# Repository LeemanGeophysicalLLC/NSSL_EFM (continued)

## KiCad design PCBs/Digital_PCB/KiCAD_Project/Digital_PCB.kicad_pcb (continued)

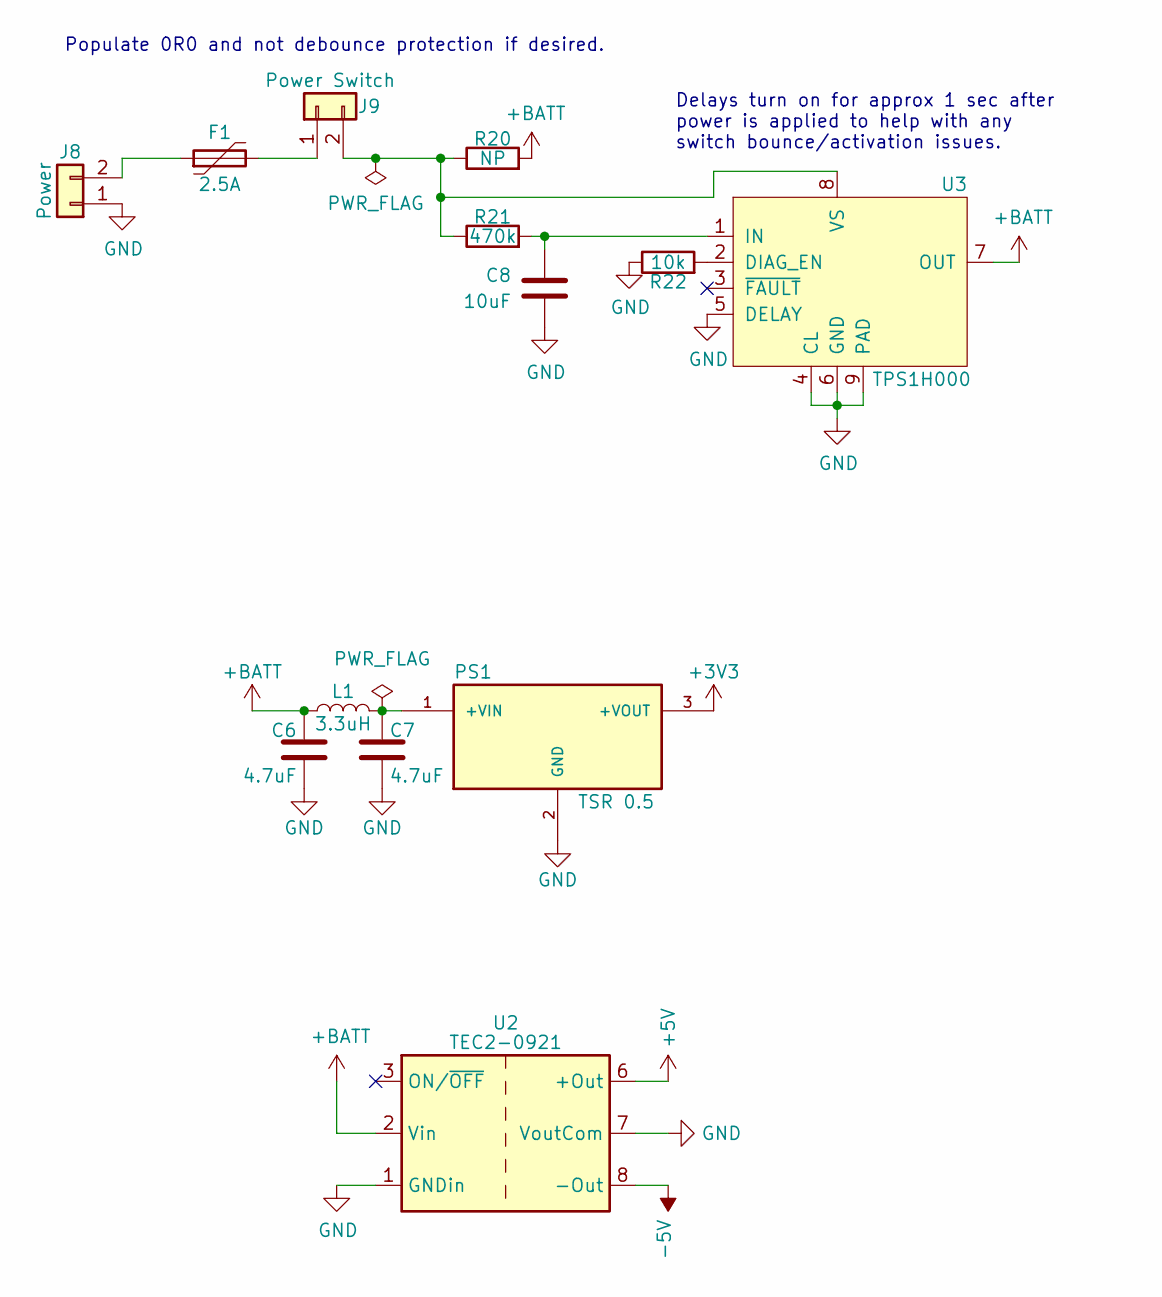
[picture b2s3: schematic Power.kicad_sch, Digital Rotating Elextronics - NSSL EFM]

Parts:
C6, C7: 1-0000136
C8: 1-0000075
F1: 1-0000269
J8, J9: NP_Conn_01x02_Relief; SolderWire_1x02_Relief
L1: 1-0000931
PS1: 1-0000727
R20: 1-0000006
R21: 1-0000068
R22: 1-0000010
U2: 1-0000465
U3: 1-0000576

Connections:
+3V3: PS1.3 (+VOUT); also elsewhere on the board
+5V: U2.6 (+Out); also elsewhere on the board
+BATT: C6.1, L1.1, R20.2, U2.2 (Vin), U3.7 (OUT); also elsewhere on the board
-5V: U2.8 (-Out); also elsewhere on the board
GND: C6.2, C7.2, C8.1, J8.1, PS1.2 (GND), R22.1, U2.1 (GNDin), U2.7 (VoutCom), U3.4 (CL), U3.5 (DELAY), U3.6 (GND), U3.9 (PAD); also elsewhere on the board
unnamed: F1.1, J8.2
unnamed: F1.2, J9.1
unnamed: J9.2, R20.1, R21.1, U3.8 (VS)
unnamed: C7.1, L1.2, PS1.1 (+VIN)
unnamed: R22.2, U3.2 (DIAG_EN)
unnamed: C8.2, R21.2, U3.1 (IN)

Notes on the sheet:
Populate 0R0 and not debounce protection if desired.
Delays turn on for approx 1 sec after power is applied to help with any switch bounce/activation issues.

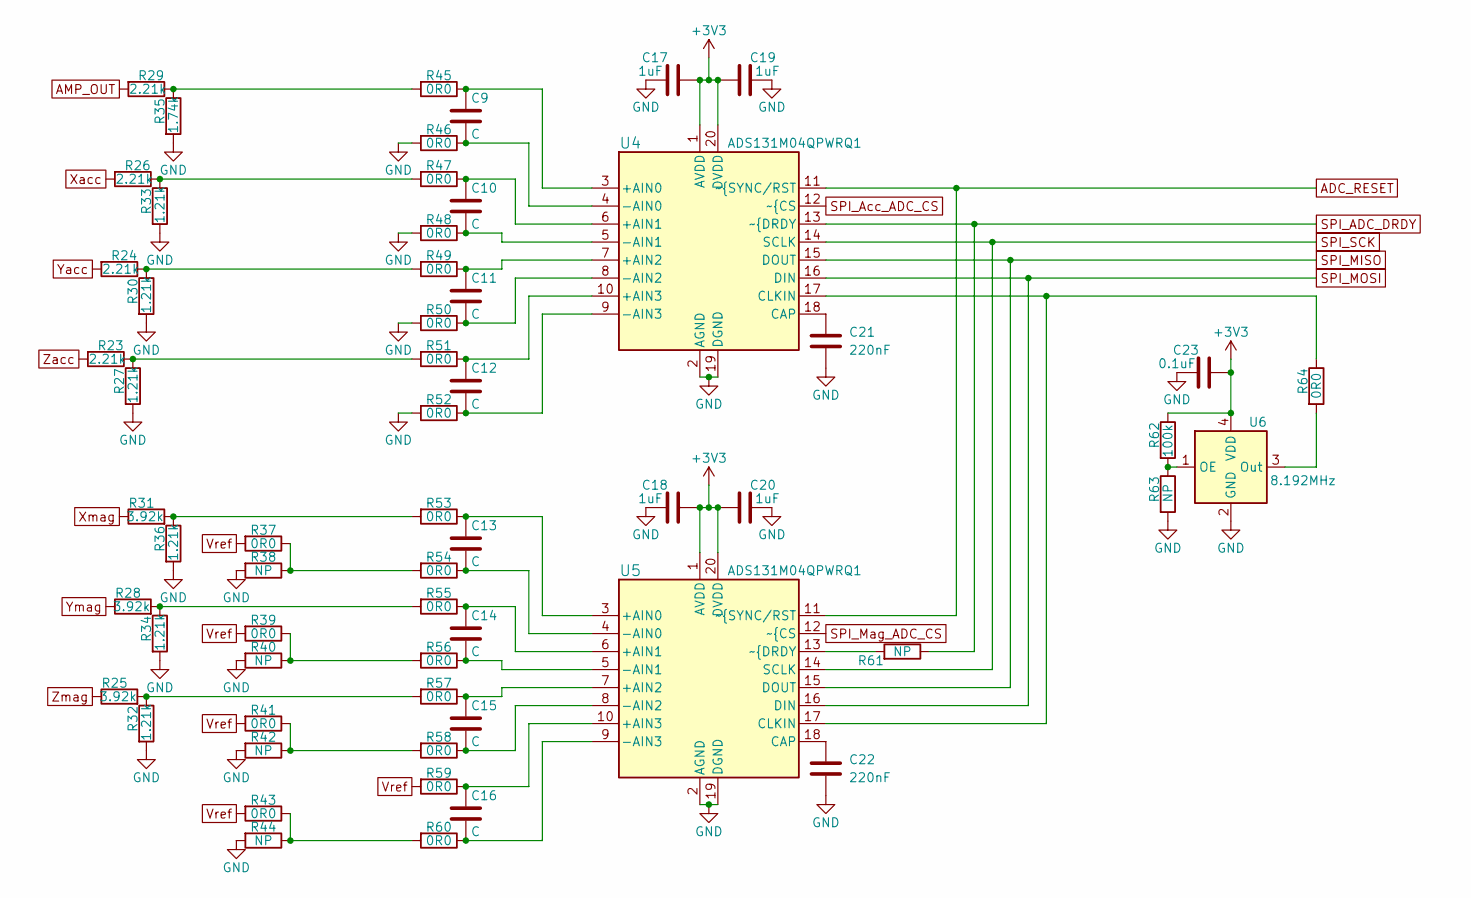
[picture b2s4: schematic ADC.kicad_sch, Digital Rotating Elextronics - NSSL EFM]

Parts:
C9, C10, C11, C12, C13, C14, C15, C16: C; C_0603_1608Metric
C17, C18, C19, C20: 1-0000018
C21, C22: 1-0000926
C23: 1-0000007
R23, R24, R26, R29: 1-0001551
R25, R28, R31: 1-0001554
R27, R30, R32, R33, R34, R36: 1-0001553
R35: 1-0001552
R37, R38, R39, R40, R41, R42, R43, R44, R45, R46, R47, R48, R49, R50, R51, R52, R53, R54, R55, R56, R57, R58, R59, R60, R61, R63, R64: 1-0000006
R62: 1-0000174
U4, U5: 1-0001530
U6: 1-0001542

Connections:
+3V3: C17.1, C18.1, C19.1, C20.1, C23.2, R62.1, U4.1 (AVDD), U4.20 (DVDD), U5.1 (AVDD), U5.20 (DVDD), U6.4 (VDD); also elsewhere on the board
ADC_RESET: U4.11 (~{SYNC/RST), U5.11 (~{SYNC/RST); also elsewhere on the board
AMP_OUT: R29.2; also elsewhere on the board
GND: C17.2, C18.2, C19.2, C20.2, C21.2, C22.2, C23.1, R27.2, R30.2, R32.2, R33.2, R34.2, R35.2, R36.2, R38.2, R40.2, R42.2, R44.2, R46.2, R48.2, R50.2, R52.2, R63.2, U4.2 (AGND), U4.19 (DGND), U5.2 (AGND), U5.19 (DGND), U6.2 (GND); also elsewhere on the board
unnamed: R23.1, R27.1, R51.2
unnamed: R24.1, R30.1, R49.2
unnamed: R25.2, R32.1, R57.2
unnamed: R26.1, R33.1, R47.2
unnamed: R28.2, R34.1, R55.2
unnamed: R29.1, R35.1, R45.2
unnamed: R31.2, R36.1, R53.2
unnamed: R37.1, R38.1, R54.2
unnamed: R39.1, R40.1, R56.2
unnamed: R41.1, R42.1, R58.2
unnamed: R43.1, R44.1, R60.2
unnamed: C9.1, R45.1, U4.3 (+AIN0)
unnamed: C10.1, R47.1, U4.6 (+AIN1)
unnamed: C11.1, R49.1, U4.7 (+AIN2)
unnamed: C12.1, R51.1, U4.10 (+AIN3)
unnamed: C9.2, R46.1, U4.4 (-AIN0)
unnamed: C10.2, R48.1, U4.5 (-AIN1)
unnamed: C11.2, R50.1, U4.8 (-AIN2)
unnamed: C12.2, R52.1, U4.9 (-AIN3)
unnamed: C21.1, U4.18 (CAP)
unnamed: R64.1, U4.17 (CLKIN), U5.17 (CLKIN)
unnamed: C13.1, R53.1, U5.3 (+AIN0)
unnamed: C14.1, R55.1, U5.6 (+AIN1)
unnamed: C15.1, R57.1, U5.7 (+AIN2)
unnamed: C16.1, R59.1, U5.10 (+AIN3)
unnamed: C13.2, R54.1, U5.4 (-AIN0)
unnamed: C14.2, R56.1, U5.5 (-AIN1)
unnamed: C15.2, R58.1, U5.8 (-AIN2)
unnamed: C16.2, R60.1, U5.9 (-AIN3)
unnamed: C22.1, U5.18 (CAP)
unnamed: R61.2, U5.13 (~{DRDY)
unnamed: R62.2, R63.1, U6.1 (OE)
unnamed: R64.2, U6.3 (Out)
SPI_ADC_DRDY: R61.1, U4.13 (~{DRDY); also elsewhere on the board
SPI_Acc_ADC_CS: U4.12 (~{CS); also elsewhere on the board
SPI_MISO: U4.15 (DOUT), U5.15 (DOUT); also elsewhere on the board
SPI_MOSI: U4.16 (DIN), U5.16 (DIN); also elsewhere on the board
SPI_Mag_ADC_CS: U5.12 (~{CS); also elsewhere on the board
SPI_SCK: U4.14 (SCLK), U5.14 (SCLK); also elsewhere on the board
Vref: R37.2, R39.2, R41.2, R43.2, R59.2; also elsewhere on the board
Xacc: R26.2; also elsewhere on the board
Xmag: R31.1; also elsewhere on the board
Yacc: R24.2; also elsewhere on the board
Ymag: R28.1; also elsewhere on the board
Zacc: R23.2; also elsewhere on the board
Zmag: R25.1; also elsewhere on the board

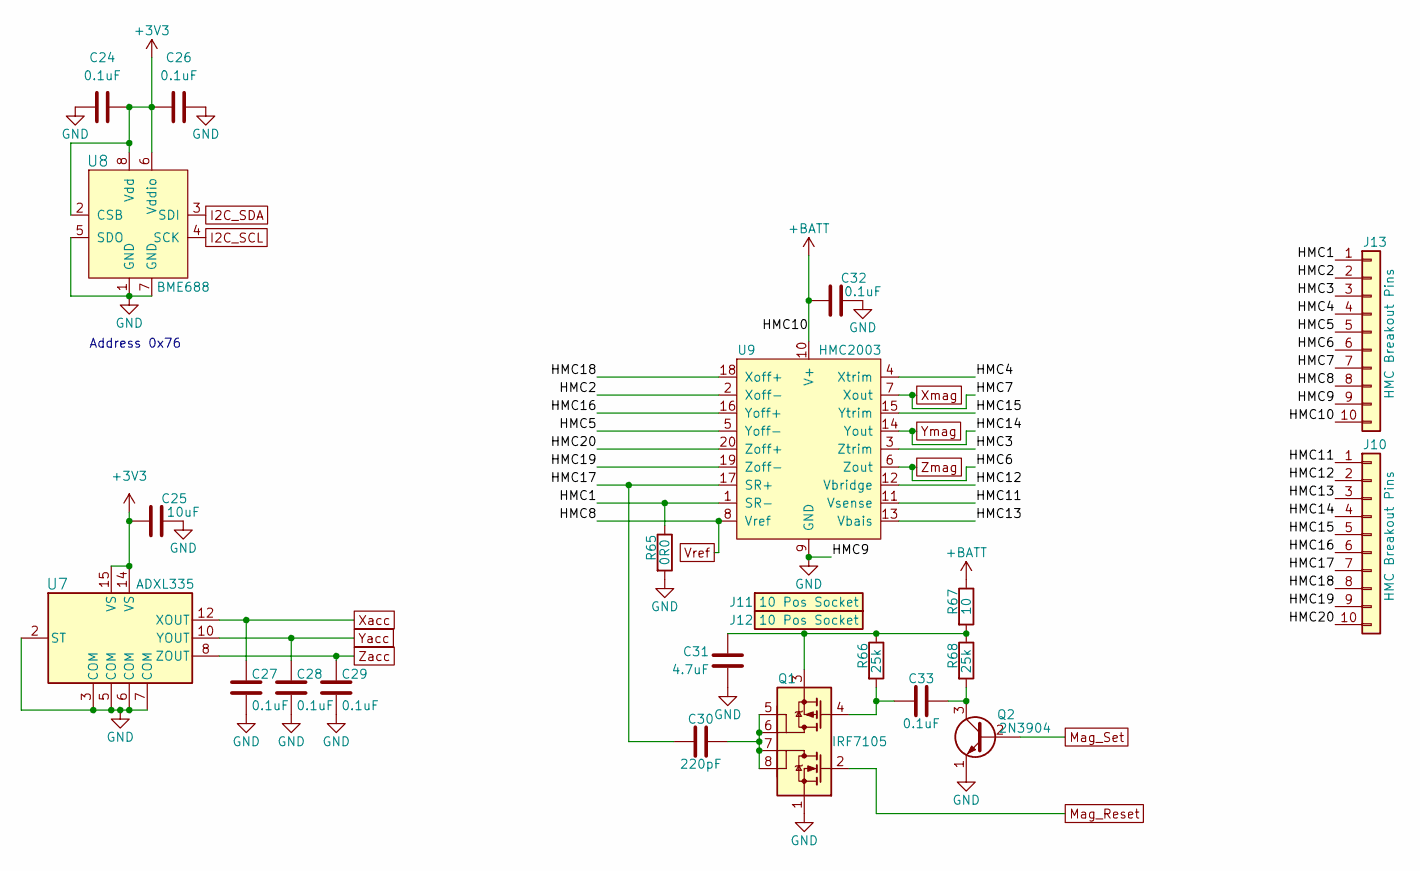
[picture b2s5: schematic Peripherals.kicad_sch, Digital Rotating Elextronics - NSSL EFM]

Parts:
C24, C26, C27, C28, C29, C32, C33: 1-0000007
C25: 1-0000075
C30: 1-0000322
C31: 1-0000136
J10, J13: HMC Breakout Pins; PinHeader_1x10_P2.54mm_Vertical
J11, J12: 1-0001555
Q1: 1-0001548
Q2: 1-0001214
R65: 1-0000006
R66, R68: 1-0001549
R67: 1-0001528
U7: 1-0001535
U8: 1-0001471
U9: 1-0001543

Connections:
+3V3: C24.2, C25.1, C26.1, U7.14 (VS), U7.15 (VS), U8.2 (CSB), U8.6 (Vddio), U8.8 (Vdd); also elsewhere on the board
+BATT: C32.1, J13.10, R67.1, U9.10 (V+); also elsewhere on the board
/Peripherals/HMC1: J13.1, R65.1, U9.1 (SR-)
/Peripherals/HMC2: J13.2, U9.2 (Xoff-)
/Peripherals/HMC3: J13.3, U9.3 (Ztrim)
/Peripherals/HMC4: J13.4, U9.4 (Xtrim)
/Peripherals/HMC5: J13.5, U9.5 (Yoff-)
/Peripherals/HMC11: J10.1, U9.11 (Vsense)
/Peripherals/HMC12: J10.2, U9.12 (Vbridge)
/Peripherals/HMC13: J10.3, U9.13 (Vbais)
/Peripherals/HMC15: J10.5, U9.15 (Ytrim)
/Peripherals/HMC16: J10.6, U9.16 (Yoff+)
/Peripherals/HMC17: C30.1, J10.7, U9.17 (SR+)
/Peripherals/HMC18: J10.8, U9.18 (Xoff+)
/Peripherals/HMC19: J10.9, U9.19 (Zoff-)
/Peripherals/HMC20: J10.10, U9.20 (Zoff+)
GND: C24.1, C25.2, C26.2, C27.2, C28.2, C29.2, C31.2, C32.2, J13.9, Q1.1 (S1), Q2.1 (E), R65.2, U7.2 (ST), U7.3 (COM), U7.5 (COM), U7.6 (COM), U7.7 (COM), U8.1 (GND), U8.5 (SDO), U8.7 (GND), U9.9 (GND); also elsewhere on the board
I2C_SCL: U8.4 (SCK); also elsewhere on the board
I2C_SDA: U8.3 (SDI); also elsewhere on the board
Mag_Reset: Q1.2 (G1); also elsewhere on the board
Mag_Set: Q2.2 (B); also elsewhere on the board
unnamed: C30.2, Q1.5 (D2), Q1.6 (D2), Q1.7 (D1), Q1.8 (D1)
unnamed: C33.1, Q1.4 (G2), R66.2
unnamed: C31.1, Q1.3 (S2), R66.1, R67.2, R68.1
unnamed: C33.2, Q2.3 (C), R68.2
Vref: J13.8, U9.8 (Vref); also elsewhere on the board
Xacc: C27.1, U7.12 (XOUT); also elsewhere on the board
Xmag: J13.7, U9.7 (Xout); also elsewhere on the board
Yacc: C28.1, U7.10 (YOUT); also elsewhere on the board
Ymag: J10.4, U9.14 (Yout); also elsewhere on the board
Zacc: C29.1, U7.8 (ZOUT); also elsewhere on the board
Zmag: J13.6, U9.6 (Zout); also elsewhere on the board

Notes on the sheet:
Address 0x76

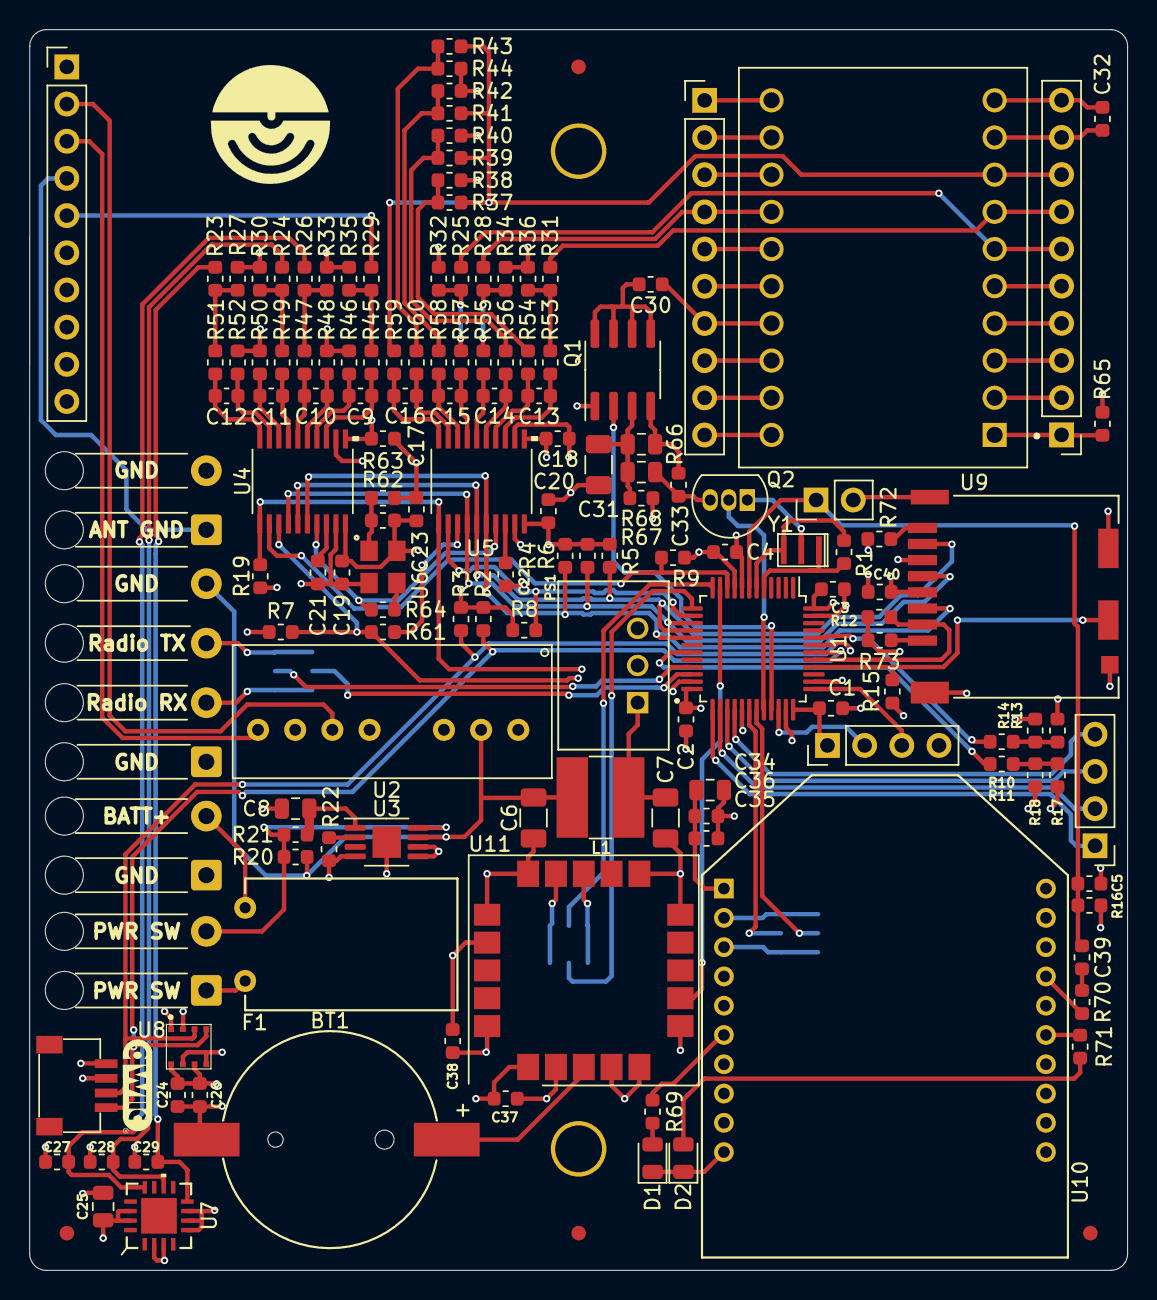
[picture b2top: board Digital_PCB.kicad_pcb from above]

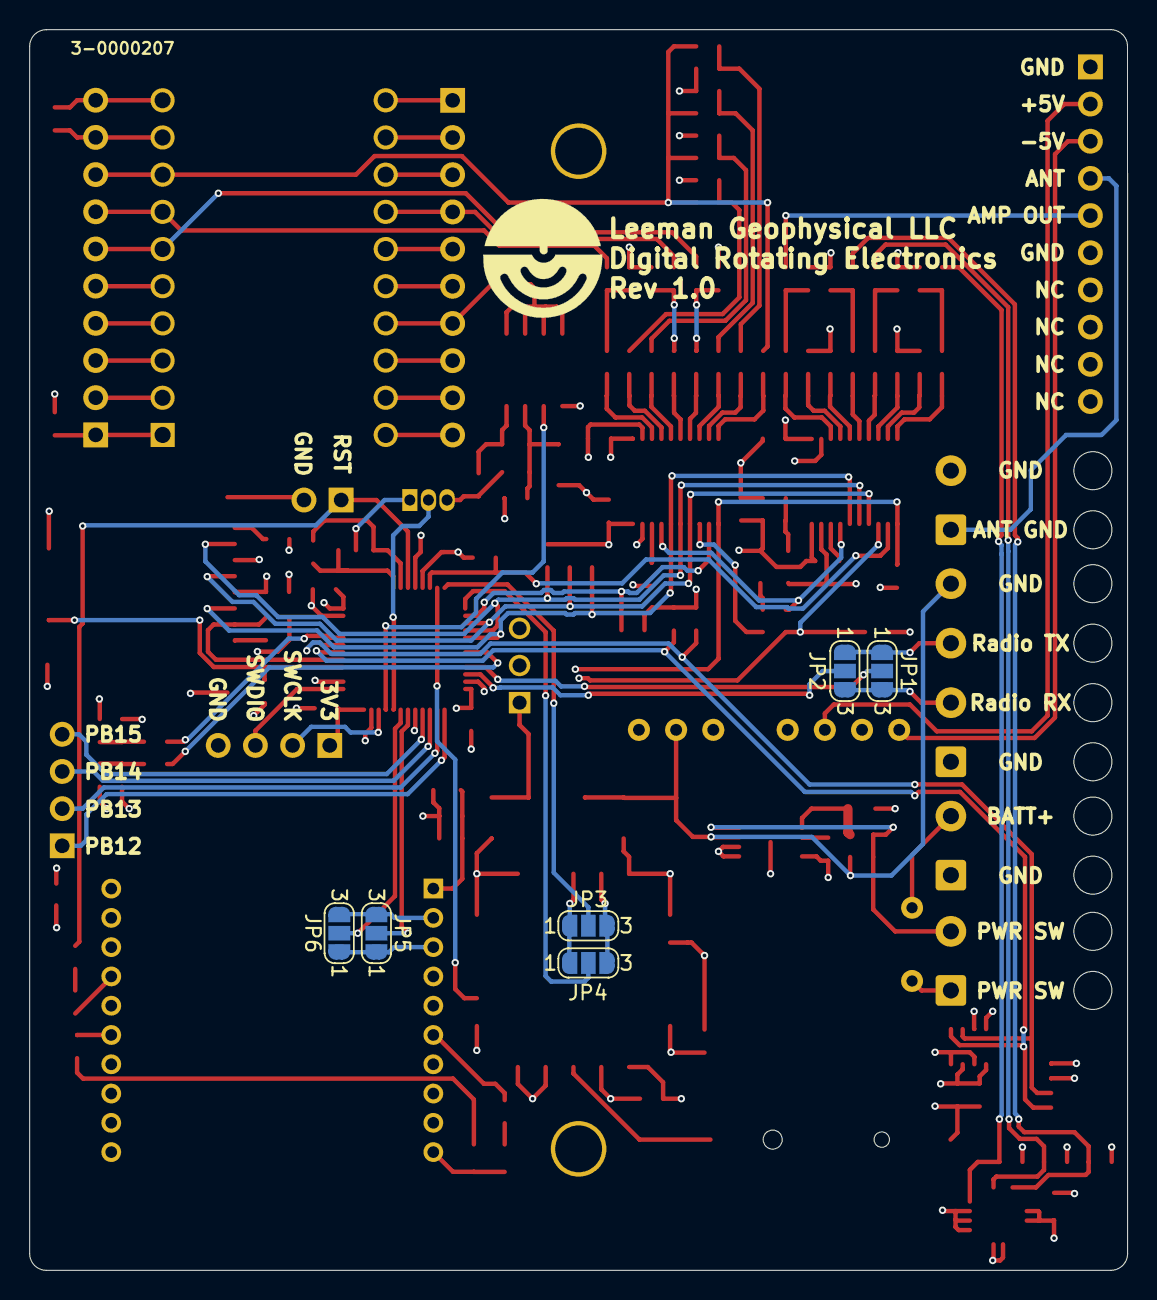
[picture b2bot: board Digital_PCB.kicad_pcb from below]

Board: 4 copper layers, 75.0 x 84.8 mm, 161 parts (6 on the bottom side), 119 nets.

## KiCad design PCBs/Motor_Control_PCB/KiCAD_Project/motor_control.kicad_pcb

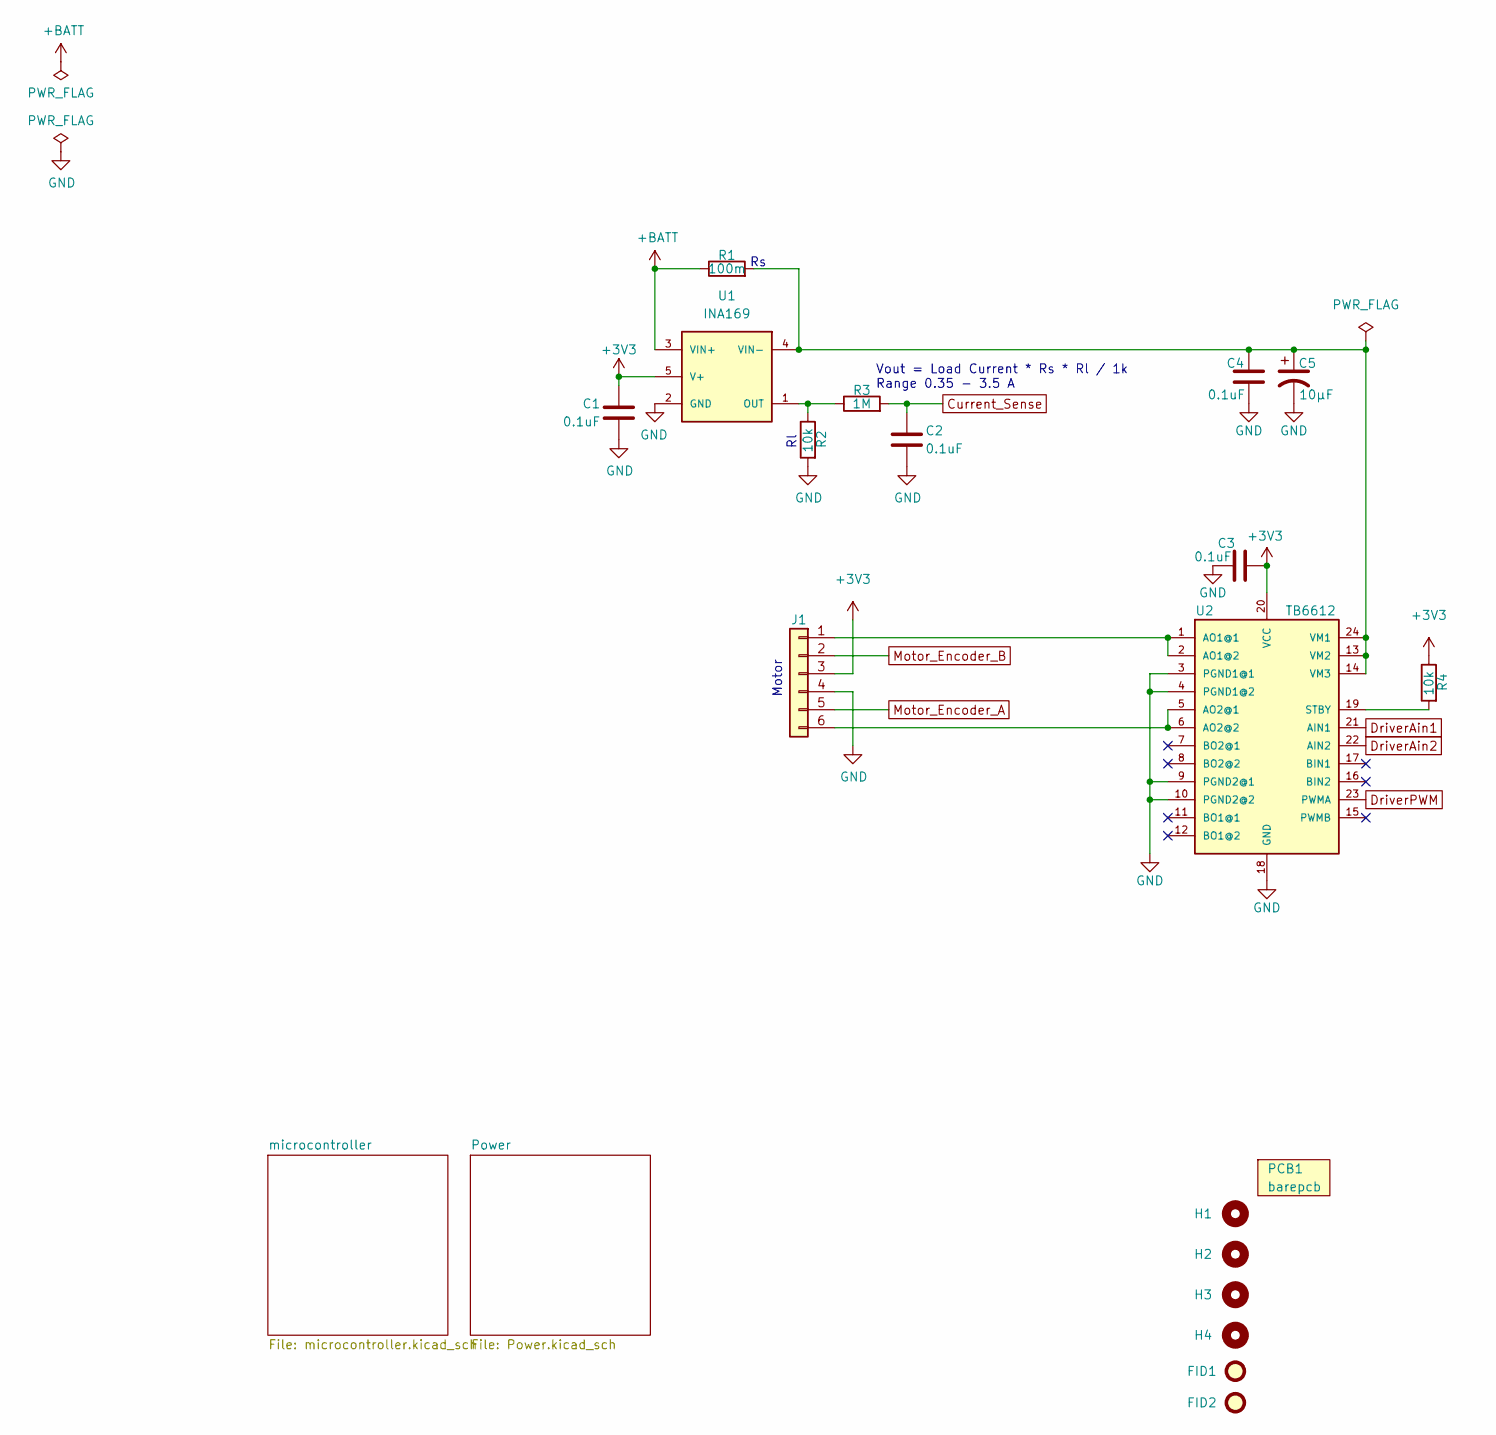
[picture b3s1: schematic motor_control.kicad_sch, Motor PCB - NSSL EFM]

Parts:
C1, C2, C3, C4: 1-0000007
C5: 1-0000176
FID1, FID2: Fiducial_1mm_2mm; Fiducial_1mm_Mask2mm
H1, H2, H3, H4: Imperial4; MountingHole_imperial4
J1: NP_Conn_01x06; PinHeader_1x06_P2.54mm_Vertical
PCB1: barepcb
R1: 1-0001546
R2, R4: 1-0000010
R3: 1-0000009
U1: 1-0000452
U2: 1-0001532

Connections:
+3V3: C1.1, C3.2, J1.3, R4.1, U1.5 (V+), U2.20 (VCC); also elsewhere on the board
+BATT: R1.1, U1.3 (VIN+); also elsewhere on the board
Current_Sense: C2.1, R3.2; also elsewhere on the board
DriverAin1: U2.21 (AIN1); also elsewhere on the board
DriverAin2: U2.22 (AIN2); also elsewhere on the board
DriverPWM: U2.23 (PWMA); also elsewhere on the board
GND: C1.2, C2.2, C3.1, C4.1, C5.2, J1.4, R2.2, U1.2 (GND), U2.3 (PGND1@1), U2.4 (PGND1@2), U2.9 (PGND2@1), U2.10 (PGND2@2), U2.18 (GND); also elsewhere on the board
Motor_Encoder_A: J1.5; also elsewhere on the board
Motor_Encoder_B: J1.2; also elsewhere on the board
unnamed: J1.1, U2.1 (AO1@1), U2.2 (AO1@2)
unnamed: J1.6, U2.5 (AO2@1), U2.6 (AO2@2)
unnamed: R2.1, R3.1, U1.1 (OUT)
unnamed: C4.2, C5.1, R1.2, U1.4 (VIN-), U2.13 (VM2), U2.14 (VM3), U2.24 (VM1)
unnamed: R4.2, U2.19 (STBY)

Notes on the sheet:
Motor
Vout = Load Current * Rs * Rl / 1k Range 0.35 - 3.5 A

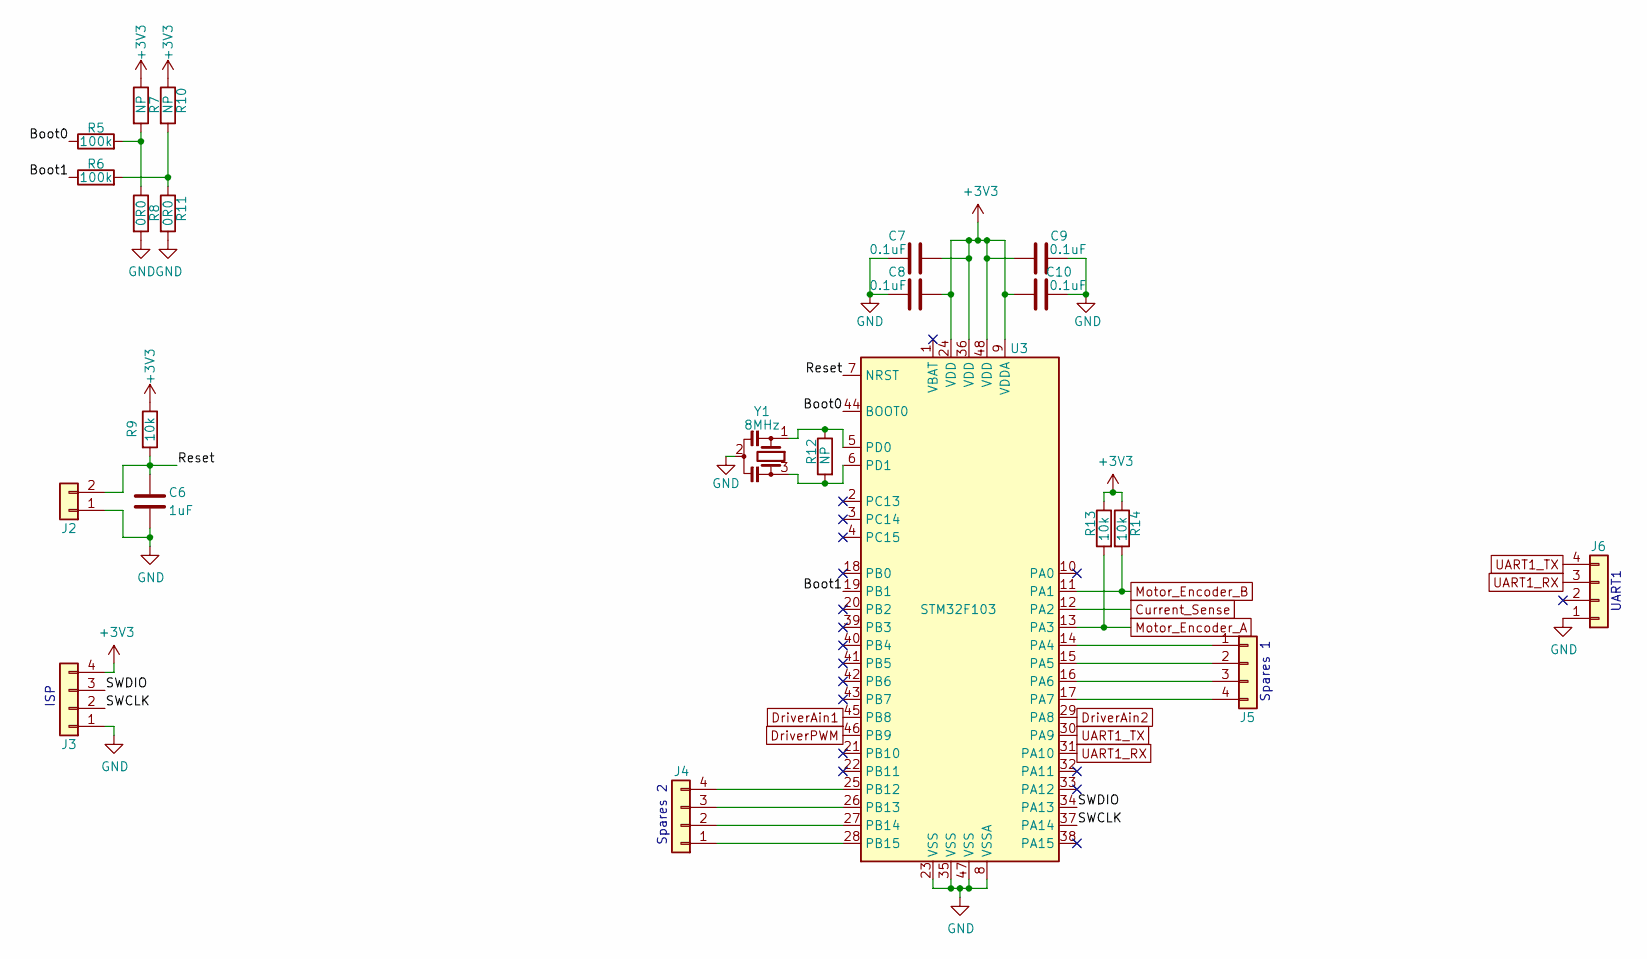
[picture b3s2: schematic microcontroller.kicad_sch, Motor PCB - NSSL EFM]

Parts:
C6: 1-0000018
C7, C8, C9, C10: 1-0000007
J2: NP_Conn_01x02; PinHeader_1x02_P2.54mm_Vertical
J3, J4, J5, J6: NP_Conn_01x04; PinHeader_1x04_P2.54mm_Vertical
R5, R6: 1-0000174
R7, R8, R10, R11, R12: 1-0000006
R9, R13, R14: 1-0000010
U3: 1-0000207
Y1: 1-0000721

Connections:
+3V3: C7.1, C8.1, C9.1, C10.1, J3.4, R7.1, R9.1, R10.1, R13.1, R14.1, U3.9 (VDDA), U3.24 (VDD), U3.36 (VDD), U3.48 (VDD); also elsewhere on the board
/microcontroller/Boot0: R5.1, U3.44 (BOOT0)
/microcontroller/Boot1: R6.1, U3.19 (PB1)
/microcontroller/Reset: C6.1, J2.2, R9.2, U3.7 (NRST)
/microcontroller/SWCLK: J3.2, U3.37 (PA14)
/microcontroller/SWDIO: J3.3, U3.34 (PA13)
Current_Sense: U3.12 (PA2); also elsewhere on the board
DriverAin1: U3.45 (PB8); also elsewhere on the board
DriverAin2: U3.29 (PA8); also elsewhere on the board
DriverPWM: U3.46 (PB9); also elsewhere on the board
GND: C6.2, C7.2, C8.2, C9.2, C10.2, J2.1, J3.1, J6.1, R8.2, R11.2, U3.8 (VSSA), U3.23 (VSS), U3.35 (VSS), U3.47 (VSS), Y1.2; also elsewhere on the board
Motor_Encoder_A: R13.2, U3.13 (PA3); also elsewhere on the board
Motor_Encoder_B: R14.2, U3.11 (PA1); also elsewhere on the board
unnamed: J4.1, U3.28 (PB15)
unnamed: J4.2, U3.27 (PB14)
unnamed: J4.3, U3.26 (PB13)
unnamed: J4.4, U3.25 (PB12)
unnamed: J5.1, U3.14 (PA4)
unnamed: J5.2, U3.15 (PA5)
unnamed: J5.3, U3.16 (PA6)
unnamed: J5.4, U3.17 (PA7)
unnamed: R5.2, R7.2, R8.1
unnamed: R6.2, R10.2, R11.1
unnamed: R12.1, U3.5 (PD0), Y1.1
unnamed: R12.2, U3.6 (PD1), Y1.3
UART1_RX: J6.3, U3.31 (PA10)
UART1_TX: J6.4, U3.30 (PA9)

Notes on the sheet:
Spares 1
UART1
Spares 2
ISP

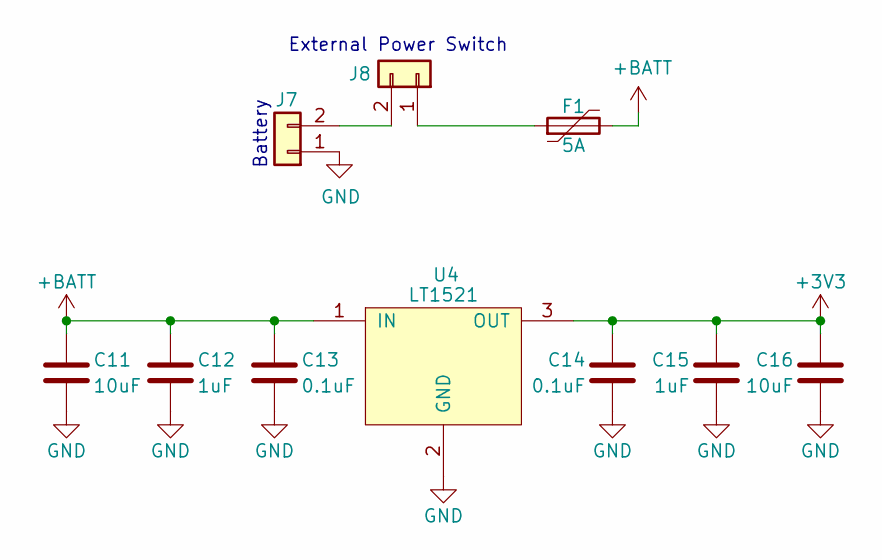
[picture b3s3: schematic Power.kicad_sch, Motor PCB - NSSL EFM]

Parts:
C11, C16: 1-0000005
C12, C15: 1-0000018
C13, C14: 1-0000007
F1: 1-0001547
J7, J8: NP_Conn_01x02_Relief; SolderWire_1x02_Relief
U4: 1-0000196

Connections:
+3V3: C14.1, C15.1, C16.1, U4.3 (OUT); also elsewhere on the board
+BATT: C11.1, C12.1, C13.1, F1.2, U4.1 (IN); also elsewhere on the board
GND: C11.2, C12.2, C13.2, C14.2, C15.2, C16.2, J7.1, U4.2 (GND); also elsewhere on the board
unnamed: J7.2, J8.2
unnamed: F1.1, J8.1

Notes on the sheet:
Battery
External Power Switch

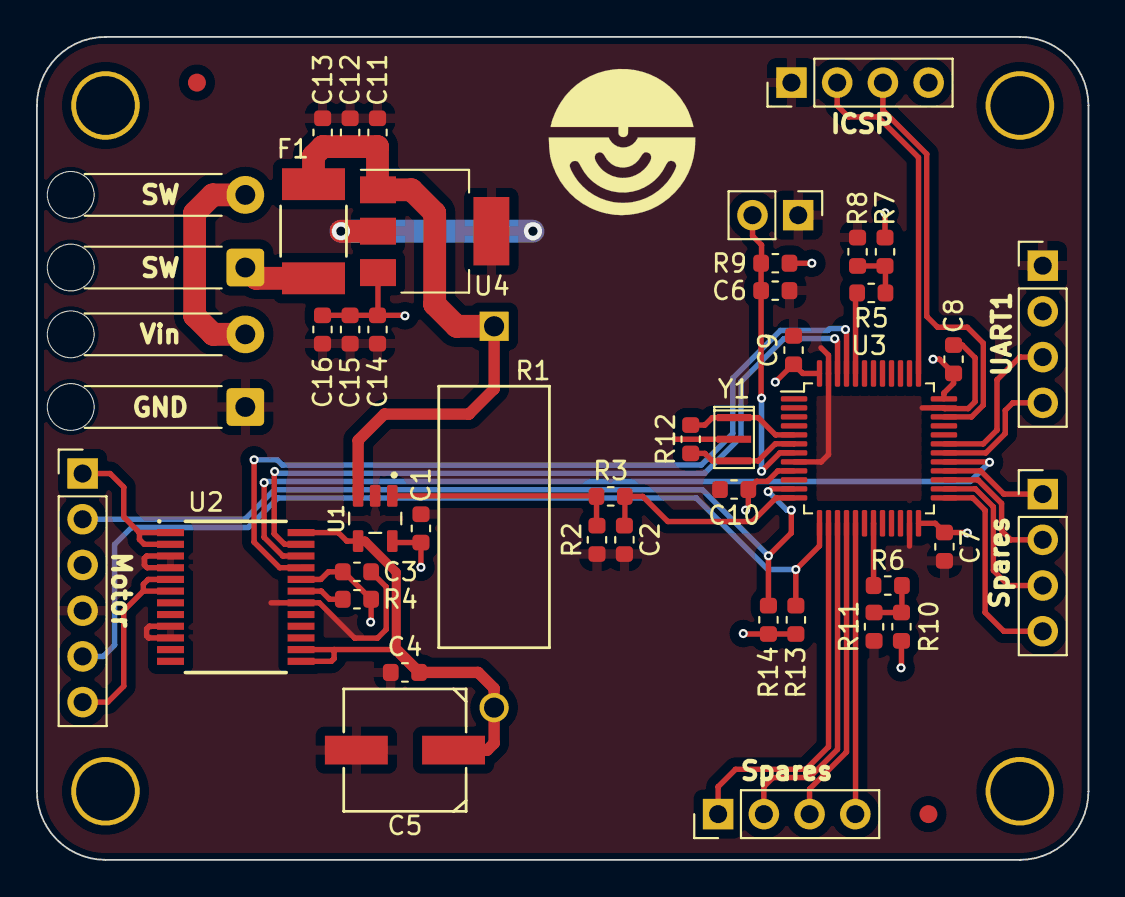
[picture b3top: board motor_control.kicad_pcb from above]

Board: 4 copper layers, 58.4 x 45.7 mm, 51 parts (0 on the bottom side), 35 nets.

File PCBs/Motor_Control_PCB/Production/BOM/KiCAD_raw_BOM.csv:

"Reference","Value","Datasheet","Footprint","Qty","Internal Part Number","PValue","Populated"
"C1","1-0000007","~","capacitors_0603:1-0000007","1","1-0000007","0.1uF","1"
"C2","1-0000007","~","capacitors_0603:1-0000007","1","1-0000007","0.1uF","1"
"C3","1-0000007","~","capacitors_0603:1-0000007","1","1-0000007","0.1uF","1"
"C4","1-0000007","~","capacitors_0603:1-0000007","1","1-0000007","0.1uF","1"
"C5","1-0000176","~","capacitors:1-0000176","1","1-0000176","10µF","1"
"C6","1-0000018","~","capacitors_0603:1-0000018","1","1-0000018","1uF","1"
"C7","1-0000007","~","capacitors_0603:1-0000007","1","1-0000007","0.1uF","1"
"C8","1-0000007","~","capacitors_0603:1-0000007","1","1-0000007","0.1uF","1"
"C9","1-0000007","~","capacitors_0603:1-0000007","1","1-0000007","0.1uF","1"
"C10","1-0000007","~","capacitors_0603:1-0000007","1","1-0000007","0.1uF","1"
"C11","1-0000005","~","capacitors_0603:1-0000005","1","1-0000005","10uF","1"
"C12","1-0000018","~","capacitors_0603:1-0000018","1","1-0000018","1uF","1"
"C13","1-0000007","~","capacitors_0603:1-0000007","1","1-0000007","0.1uF","1"
"C14","1-0000007","~","capacitors_0603:1-0000007","1","1-0000007","0.1uF","1"
"C15","1-0000018","~","capacitors_0603:1-0000018","1","1-0000018","1uF","1"
"C16","1-0000005","~","capacitors_0603:1-0000005","1","1-0000005","10uF","1"
"F1","1-0001547","~","fuses:1-0001547","1","1-0001547","5A","1"
"FID1","Fiducial_1mm_2mm","~","mechanical:Fiducial_1mm_Mask2mm","1","0-0000000","Fiducial","0"
"FID2","Fiducial_1mm_2mm","~","mechanical:Fiducial_1mm_Mask2mm","1","0-0000000","Fiducial","0"
"H1","Imperial4","None","mechanical:MountingHole_imperial4","1","0-0000000","#4","0"
"H2","Imperial4","None","mechanical:MountingHole_imperial4","1","0-0000000","#4","0"
"H3","Imperial4","None","mechanical:MountingHole_imperial4","1","0-0000000","#4","0"
"H4","Imperial4","None","mechanical:MountingHole_imperial4","1","0-0000000","#4","0"
"J1","NP_Conn_01x06","~","np_connectors:PinHeader_1x06_P2.54mm_Vertical","1","0-0000000","01x06","0"
"J2","NP_Conn_01x02","~","np_connectors:PinHeader_1x02_P2.54mm_Vertical","1","0-0000000","NP_Conn_01x02","0"
"J3","NP_Conn_01x04","~","np_connectors:PinHeader_1x04_P2.54mm_Vertical","1","0-0000000","NP_Conn_01x04","0"
"J4","NP_Conn_01x04","~","np_connectors:PinHeader_1x04_P2.54mm_Vertical","1","0-0000000","NP_Conn_01x04","0"
"J5","NP_Conn_01x04","~","np_connectors:PinHeader_1x04_P2.54mm_Vertical","1","0-0000000","NP_Conn_01x04","0"
"J6","NP_Conn_01x04","~","np_connectors:PinHeader_1x04_P2.54mm_Vertical","1","0-0000000","NP_Conn_01x04","0"
"J7","NP_Conn_01x02_Relief","~","np_connectors:SolderWire_1x02_Relief","1","0-0000000","NP_Conn_01x02","0"
"J8","NP_Conn_01x02_Relief","~","np_connectors:SolderWire_1x02_Relief","1","0-0000000","NP_Conn_01x02","0"
"PCB1","barepcb","","misc:barepcb","1","3-0000208","Bare PCB","1"
"R1","1-0001546","~","resistors:1-0001546","1","1-0001546","100m","1"
"R2","1-0000010","~","resistors_0603:1-0000010","1","1-0000010","10k","1"
"R3","1-0000009","~","resistors_0603:1-0000009","1","1-0000009","1M","1"
"R4","1-0000010","~","resistors_0603:1-0000010","1","1-0000010","10k","1"
"R5","1-0000174","~","resistors_0603:1-0000174","1","1-0000174","100k","1"
"R6","1-0000174","~","resistors_0603:1-0000174","1","1-0000174","100k","1"
"R7","1-0000006","~","resistors_0603:1-0000006","1","1-0000006","NP","0"
"R8","1-0000006","~","resistors_0603:1-0000006","1","1-0000006","0R0","1"
"R9","1-0000010","~","resistors_0603:1-0000010","1","1-0000010","10k","1"
"R10","1-0000006","~","resistors_0603:1-0000006","1","1-0000006","NP","0"
"R11","1-0000006","~","resistors_0603:1-0000006","1","1-0000006","0R0","1"
"R12","1-0000006","~","resistors_0603:1-0000006","1","1-0000006","NP","0"
"R13","1-0000010","~","resistors_0603:1-0000010","1","1-0000010","10k","1"
"R14","1-0000010","~","resistors_0603:1-0000010","1","1-0000010","10k","1"
"U1","1-0000452","","others:1-0000452","1","1-0000452","INA169","1"
"U2","1-0001532","","motor_drivers:1-0001532","1","1-0001532","TB6612","1"
"U3","1-0000207","","microcontrollers:1-0000207","1","1-0000207","STM32F103","1"
"U4","1-0000196","","regulators:1-0000196","1","1-0000196","LT1521","1"
"Y1","1-0000721","~","crystals_resonators:1-0000721","1","1-0000721","8MHz","1"
